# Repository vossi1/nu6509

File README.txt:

Nu6509 - Adapter to use 6502 in 6509-based systemOriginal Design: Copyright (c) 2017-2019 Jim Brain dba RETRO Innovations

Copyright (c) 2023 Vossi - v.1[fixed, modified, no '816 support!]www.mos6509.com

Permission is hereby granted, free of charge, to any person obtaining a copy
of this software and associated documentation files (the "Software"), to deal
in the Software without restriction, including without limitation the rights
to use, copy, modify, merge, publish, distribute, sublicense, and/or sell
copies of the Software, and to permit persons to whom the Software is
furnished to do so, subject to the following conditions:

The above copyright notice and this permission notice shall be included in all
copies or substantial portions of the Software.

THE SOFTWARE IS PROVIDED "AS IS", WITHOUT WARRANTY OF ANY KIND, EXPRESS OR
IMPLIED, INCLUDING BUT NOT LIMITED TO THE WARRANTIES OF MERCHANTABILITY,
FITNESS FOR A PARTICULAR PURPOSE AND NONINFRINGEMENT. IN NO EVENT SHALL THE
AUTHORS OR COPYRIGHT HOLDERS BE LIABLE FOR ANY CLAIM, DAMAGES OR OTHER
LIABILITY, WHETHER IN AN ACTION OF CONTRACT, TORT OR OTHERWISE, ARISING FROM,
OUT OF OR IN CONNECTION WITH THE SOFTWARE OR THE USE OR OTHER DEALINGS IN THE
SOFTWARE.

Nu6509.v: Routines to support mapping the 6509-specific bank functionality onto the 6502.    fixed:	databus read out always active if no WRITE (not only at PHI2=high, not dependent from RDY)	databus not dependent from RDY (ready is ignored at writes, wdc allows halt in write cycles)	databus writes not dependent from AEC (original 6509 doesn't disable DB with AEC)	hardwired sync (important for timing in P500)modified:	removed 65816 support	added jtag connector	only 0805 parts	hardwired _so	solderpad is pre-connected for NMOS/CMOS 6502 -> cut for WDC W65C02S

Tested successful in cbm620 with:
	mos6502A
	mos6502B (3MHz)
	R6502AP
	UM6502A
	UMC6502CE (4MHz, nmos)
	CMD G65SC02-2
	gte G65SC02-2
	WDC W65C02S-8 (8MHz)

Tests: Diagnostic-Cart, Burnin-Test, Michal's Testsuite, Superscript
	(all cmos chips have TOD error in cbm burnin test???)

Tested successful in P500 with:
	mos6502A
	mos6502B (3MHz)
	R6502
	R6502AP
	SY6502
	UM6502A
	UMC6502CE (4MHz)
	CMD G65SC02-2
	gte G65SC02-2
	WDC W65C02S-8 (8MHz)

Tests: PacMan, Wizard of War, cbm RAM-Test (improved by Vossi), David Viner's Hires-Demo

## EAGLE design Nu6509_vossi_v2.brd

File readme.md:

# Nu6509 - Adapter to use 6502 in 6509-based system

**Original Design: Copyright (c) 2017-2019 Jim Brain dba RETRO Innovations**

**Copyright (c) 2023 Vossi - v.2** [fixed, modified, 6512 support, no '816 support]

**www.mos6509.com**

Permission is hereby granted, free of charge, to any person obtaining a copy
of this software and associated documentation files (the "Software"), to deal
in the Software without restriction, including without limitation the rights
to use, copy, modify, merge, publish, distribute, sublicense, and/or sell
copies of the Software, and to permit persons to whom the Software is
furnished to do so, subject to the following conditions:

The above copyright notice and this permission notice shall be included in all
copies or substantial portions of the Software.

THE SOFTWARE IS PROVIDED "AS IS", WITHOUT WARRANTY OF ANY KIND, EXPRESS OR
IMPLIED, INCLUDING BUT NOT LIMITED TO THE WARRANTIES OF MERCHANTABILITY,
FITNESS FOR A PARTICULAR PURPOSE AND NONINFRINGEMENT. IN NO EVENT SHALL THE
AUTHORS OR COPYRIGHT HOLDERS BE LIABLE FOR ANY CLAIM, DAMAGES OR OTHER
LIABILITY, WHETHER IN AN ACTION OF CONTRACT, TORT OR OTHERWISE, ARISING FROM,
OUT OF OR IN CONNECTION WITH THE SOFTWARE OR THE USE OR OTHER DEALINGS IN THE
SOFTWARE.

**Nu6509.v: Routines to support mapping the 6509-specific bank functionality onto the 6502.**

**[Schematic](https://github.com/vossi1/nu6509/blob/master/schematics_v2.png)**

**[Parts](https://github.com/vossi1/nu6509/blob/master/parts.txt)**

**CPLD-Firmware:** The .JED file can be uploaded with a JTAG-SMT2 Xilinx programmer (China) and [xc3sprog](https://xc3sprog.sourceforge.net/)

**USE v.2 HDL-code in Folder HDL-P500 for the P500 - for the 6xx, 7xx v.2 and v.2a are ok**

**Fixed:**

	databus not dependent from RDY (ready is ignored at writes, wdc allows halt in write cycles)
	databus read and write with 30ns hold time after PHI2 falling edge
	hardwired SYNC (important for timing in P500)

**Modified:**

	removed 65816 support
	added jtag connector
	only 0805 parts
	hardwired _SO
	solderpad is pre-connected for NMOS/CMOS 6502 -> cut for WDC W65C02S
	added 6512 support with solderpad for PHI1 in from 6509 socket

:x: **BEWARE: XC9572 from China are mostly FAKES - many of them work - but you don't know what you get!**

Notes:
In low profile machines there is not enough space in the height to insert the adapter with socket. There is even less space in devices with a bottom-mounted power supply unit. The only solution is to first test the NU6509 in an open device and then solder it directly into the board.
The NU6509 does not support AEC! No known CBMII-machine uses it - AEC is always pulled up on all CBMII-boards.
If you encounter problems with a specific 6502 CPU, try another one - best choice is mostly an old mos 6502A.

**Tested successful in cbm2 with:** Diagnostic, Burnin-Test, Testsuite, Superscript, Monitor D.Viner, Supermon, Diskview

Test-boards: 610 Rev.E, 620 Rev.F, 710 Rev.B, 710 Rev.C, 720 Rev. B

	mos6502A
	mos6502AD
	mos6502B (3MHz)
	R6502AP
	UM6502A
	UM6502B (3MHz, nmos)
	UM6502CE (4MHz, nmos)
	R65C02P2 (cmos)
	R65C02-J4 (4MHz, cmos, in PLCC Adapter)
	gteµ G65SC02P-2 (cmos)
	CMD G65SC02PI-2 (cmos)
	CMD G65SC02PE-4 (4MHz, cmos, in PLCC Adapter)
	WDC W65C02S8PL-10 (10MHz, cmos, in PLCC Adapter)

	R6512AP (with Solderpad 6512 for PHI1 - needs the two-phase clock!)
	GTEµ G65SC12P-2 (2MHz, cmos) (with Solderpad 6512 for PHI1 - needs the two-phase clock!)

Note cmos: (all cmos chips have TOD error in the cbm2 burnin test - localized at indirect read from CIA registers - so they are probably unusable?)

**Tested successful in P500 EU with:** pm500, wiz500, amind500 (all converted by vossi), P500-Test (finished & improved by Vossi), David Viner's Hires-Demo

	mos6502
	mos6502AD
	mos6502A
	mos6502B (3MHz)
	R6502
	R6502AP
	SY6502
	UM6502
	UM6502A
	UM6502B (3MHz, nmos)
	UM6502CE (4MHz, nmos)
	R65C02P2 (cmos)
	R65C02-J4 (4MHz, cmos, in PLCC Adapter)
	gteµ G65SC02P-2 (cmos)
	CMD G65SC02PI-2 (cmos)
	CMD G65SC02PE-4 (4MHz, cmos, in PLCC Adapter)
	WDC W65C02S8PL-10 (10MHz, cmos, in PLCC Adapter)

	R6512AP (with Solderpad 6512 for PHI1 - needs the two-phase clock!)
	GTEµ G65SC12P-2 (with Solderpad 6512 for PHI1 - needs the two-phase clock!)

Note cmos: (amind 500 uses illegal opcodes and doesn't run on cmos CPU's)
Note cmos: (all cmos chips have also TOD error in my new P500-test v. 1.4 - so they are probably unusable?)

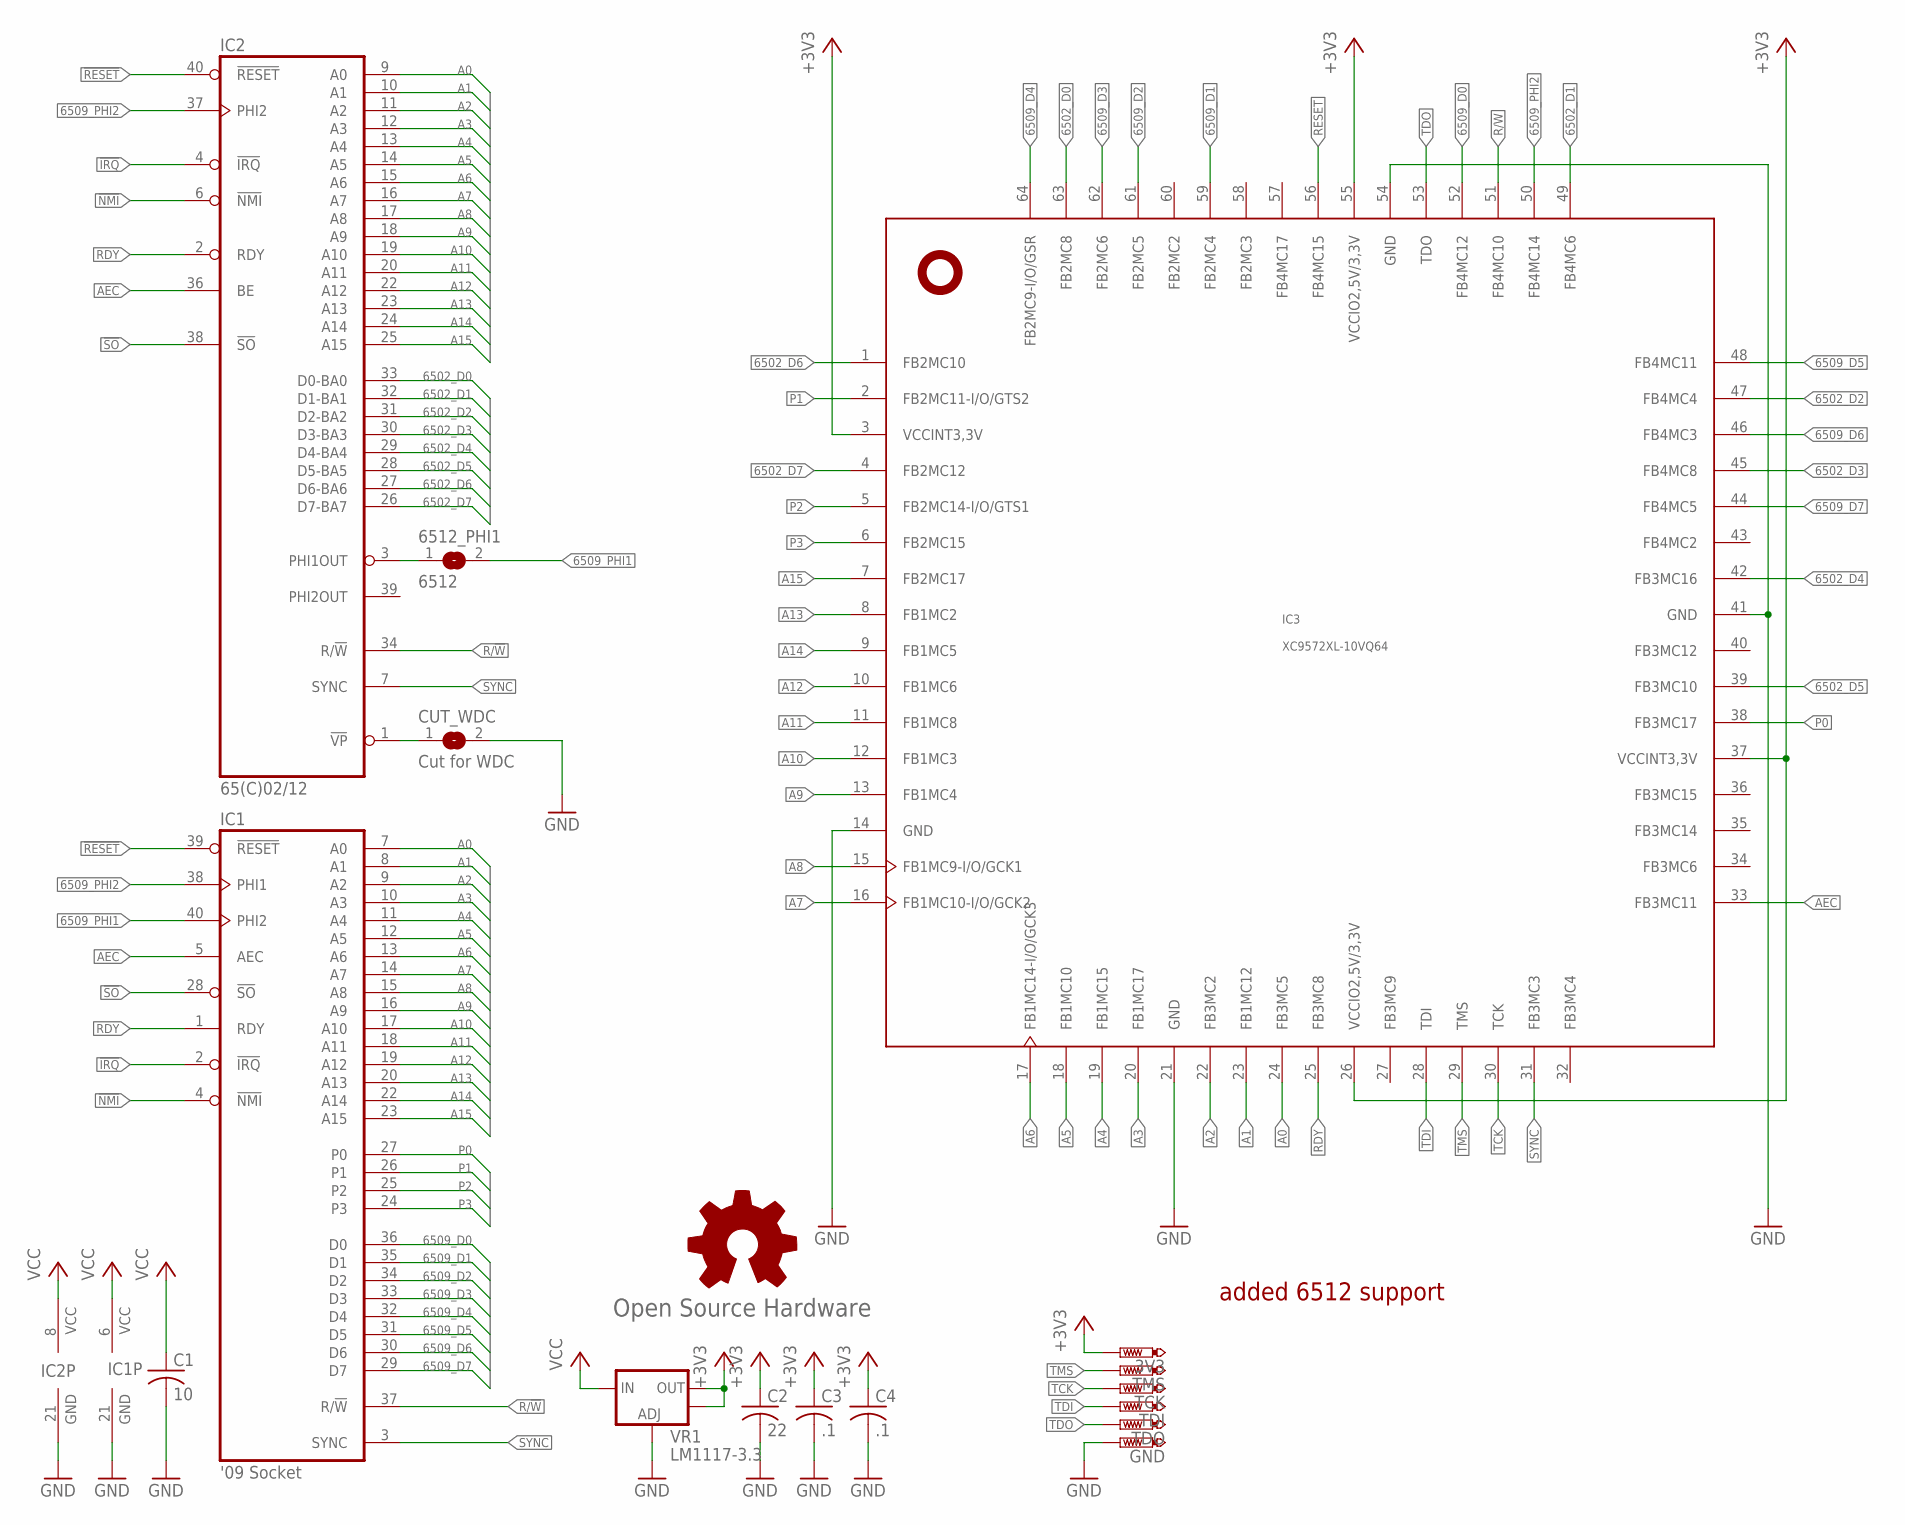
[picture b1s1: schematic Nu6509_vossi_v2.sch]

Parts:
3V3: PTR1TP08R; TP08R
6512_PHI1: 6512; SJ
C1: 10; C0805
C2: 22; C0805
C3, C4: .1; C0805
CUT_WDC: Cut for WDC; SJ
GND: PTR1TP08R; TP08R
GOLD_ORB_SM1: Open Source Hardware; OSHW_5MM
IC1: '09 Socket; DIL40-ROUNDPAD
IC2: 65(C)02/12; DIL40-ROUNDPAD
IC3: XC9572XL-10VQ64; VQFP64
TCK: PTR1TP08R; TP08R
TDI: PTR1TP08R; TP08R
TDO: PTR1TP08R; TP08R
TMS: PTR1TP08R; TP08R
VR1: LM1117-3.3; SOT223

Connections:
6502_D0: IC2.33 (D0-BA0), IC3.63 (FB2MC8)
6502_D1: IC2.32 (D1-BA1), IC3.49 (FB4MC6)
6502_D2: IC2.31 (D2-BA2), IC3.47 (FB4MC4)
6502_D3: IC2.30 (D3-BA3), IC3.45 (FB4MC8)
6502_D4: IC2.29 (D4-BA4), IC3.42 (FB3MC16)
6502_D5: IC2.28 (D5-BA5), IC3.39 (FB3MC10)
6502_D6: IC2.27 (D6-BA6), IC3.1 (FB2MC10)
6502_D7: IC2.26 (D7-BA7), IC3.4 (FB2MC12)
6502_VSS: CUT_WDC.1, IC2.1 (!VP)
6509_D0: IC1.36 (D0), IC3.52 (FB4MC12)
6509_D1: IC1.35 (D1), IC3.59 (FB2MC4)
6509_D2: IC1.34 (D2), IC3.61 (FB2MC5)
6509_D3: IC1.33 (D3), IC3.62 (FB2MC6)
6509_D4: IC1.32 (D4), IC3.64 (FB2MC9-I/O/GSR)
6509_D5: IC1.31 (D5), IC3.48 (FB4MC11)
6509_D6: IC1.30 (D6), IC3.46 (FB4MC3)
6509_D7: IC1.29 (D7), IC3.44 (FB4MC5)
6509_PHI1: 6512_PHI1.2, IC1.40 (PHI2)
6509_PHI2: IC1.38 (PHI1), IC2.37 (PHI2), IC3.50 (FB4MC14)
6512_PHI1: 6512_PHI1.1, IC2.3 (PHI1OUT)
!IRQ: IC1.2 (!IRQ), IC2.4 (!IRQ)
!NMI: IC1.4 (!NMI), IC2.6 (!NMI)
!RESET: IC1.39 (!RESET), IC2.40 (!RESET), IC3.56 (FB4MC15)
!SO: IC1.28 (!SO), IC2.38 (!SO)
+3V3: 3V3.TP, C2.1, C3.1, C4.1, IC3.3 (VCCINT3,3V), IC3.26 (VCCIO2,5V/3,3V), IC3.37 (VCCINT3,3V), IC3.55 (VCCIO2,5V/3,3V), VR1.2 (OUT), VR1.4 (OUT)
A0: IC1.7 (A0), IC2.9 (A0), IC3.24 (FB3MC5)
A1: IC1.8 (A1), IC2.10 (A1), IC3.23 (FB1MC12)
A2: IC1.9 (A2), IC2.11 (A2), IC3.22 (FB3MC2)
A3: IC1.10 (A3), IC2.12 (A3), IC3.20 (FB1MC17)
A4: IC1.11 (A4), IC2.13 (A4), IC3.19 (FB1MC15)
A5: IC1.12 (A5), IC2.14 (A5), IC3.18 (FB1MC10)
A6: IC1.13 (A6), IC2.15 (A6), IC3.17 (FB1MC14-I/O/GCK3)
A7: IC1.14 (A7), IC2.16 (A7), IC3.16 (FB1MC10-I/O/GCK2)
A8: IC1.15 (A8), IC2.17 (A8), IC3.15 (FB1MC9-I/O/GCK1)
A9: IC1.16 (A9), IC2.18 (A9), IC3.13 (FB1MC4)
A10: IC1.17 (A10), IC2.19 (A10), IC3.12 (FB1MC3)
A11: IC1.18 (A11), IC2.20 (A11), IC3.11 (FB1MC8)
A12: IC1.19 (A12), IC2.22 (A12), IC3.10 (FB1MC6)
A13: IC1.20 (A13), IC2.23 (A13), IC3.8 (FB1MC2)
A14: IC1.22 (A14), IC2.24 (A14), IC3.9 (FB1MC5)
A15: IC1.23 (A15), IC2.25 (A15), IC3.7 (FB2MC17)
AEC: IC1.5 (AEC), IC2.36 (BE), IC3.33 (FB3MC11)
GND: C1.2, C2.2, C3.2, C4.2, CUT_WDC.2, GND.TP, IC1.21 (GND), IC2.21 (GND), IC3.14 (GND), IC3.21 (GND), IC3.41 (GND), IC3.54 (GND), VR1.1 (ADJ)
P0: IC1.27 (P0), IC3.38 (FB3MC17)
P1: IC1.26 (P1), IC3.2 (FB2MC11-I/O/GTS2)
P2: IC1.25 (P2), IC3.5 (FB2MC14-I/O/GTS1)
P3: IC1.24 (P3), IC3.6 (FB2MC15)
R/!W: IC1.37 (R/!W), IC2.34 (R/!W), IC3.51 (FB4MC10)
RDY: IC1.1 (RDY), IC2.2 (RDY), IC3.25 (FB3MC8)
SYNC: IC1.3 (SYNC), IC2.7 (SYNC), IC3.31 (FB3MC3)
TCK: IC3.30 (TCK), TCK.TP
TDI: IC3.28 (TDI), TDI.TP
TDO: IC3.53 (TDO), TDO.TP
TMS: IC3.29 (TMS), TMS.TP
VCC: C1.1, IC1.6 (VCC), IC2.8 (VCC), VR1.3 (IN)

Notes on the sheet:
added 6512 support

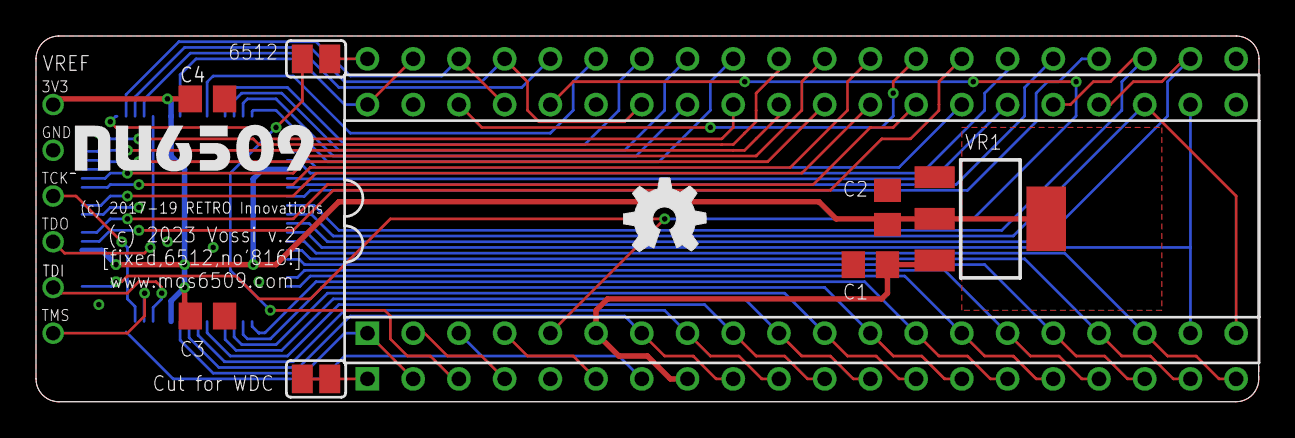
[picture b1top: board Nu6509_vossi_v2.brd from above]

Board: 2 copper layers, 67.9 x 20.3 mm, 17 parts (1 on the bottom side), 55 nets.

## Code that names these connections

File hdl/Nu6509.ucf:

#PACE: Start of Constraints generated by PACE

#PACE: Start of PACE I/O Pin Assignments
NET "_reset"  LOC = "P56"  ; 
NET "address_6502<0>"  LOC = "P24"  ; 
NET "address_6502<10>"  LOC = "P12"  ; 
NET "address_6502<11>"  LOC = "P11"  ; 
NET "address_6502<12>"  LOC = "P10"  ; 
NET "address_6502<13>"  LOC = "P8"  ; 
NET "address_6502<14>"  LOC = "P9"  ; 
NET "address_6502<15>"  LOC = "P7"  ; 
NET "address_6502<1>"  LOC = "P23"  ; 
NET "address_6502<2>"  LOC = "P22"  ; 
NET "address_6502<3>"  LOC = "P20"  ; 
NET "address_6502<4>"  LOC = "P19"  ; 
NET "address_6502<5>"  LOC = "P18"  ; 
NET "address_6502<6>"  LOC = "P17"  ; 
NET "address_6502<7>"  LOC = "P16"  ; 
NET "address_6502<8>"  LOC = "P15"  ; 
NET "address_6502<9>"  LOC = "P13"  ; 
NET "address_bank<0>"  LOC = "P38"  ; 
NET "address_bank<1>"  LOC = "P2"  ; 
NET "address_bank<2>"  LOC = "P5"  ; 
NET "address_bank<3>"  LOC = "P6"  ; 
#NET "aec"  LOC = "P33"  ; 
NET "data_6502<0>"  LOC = "P63"  ; 
NET "data_6502<1>"  LOC = "P49"  ; 
NET "data_6502<2>"  LOC = "P47"  ; 
NET "data_6502<3>"  LOC = "P45"  ; 
NET "data_6502<4>"  LOC = "P42"  ; 
NET "data_6502<5>"  LOC = "P39"  ; 
NET "data_6502<6>"  LOC = "P1"  ; 
NET "data_6502<7>"  LOC = "P4"  ; 
NET "data_6509<0>"  LOC = "P52"  ; 
NET "data_6509<1>"  LOC = "P59"  ; 
NET "data_6509<2>"  LOC = "P61"  ; 
NET "data_6509<3>"  LOC = "P62"  ; 
NET "data_6509<4>"  LOC = "P64"  ; 
NET "data_6509<5>"  LOC = "P48"  ; 
NET "data_6509<6>"  LOC = "P46"  ; 
NET "data_6509<7>"  LOC = "P44"  ; 
NET "phi2"  LOC = "P50"  ; 
NET "r_w"  LOC = "P51"  ; 
NET "rdy"  LOC = "P25"  ;
NET "sync"  LOC = "P31"  ; 

#PACE: Start of PACE Area Constraints

#PACE: Start of PACE Prohibit Constraints

#PACE: End of Constraints generated by PACE

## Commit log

2023-10-02 v1.0 initial version
2023-10-02 readme.md with photo
2023-10-02 readme.md format
2023-10-02 .git
2023-10-02 gerber
2023-10-08 added cpus
2023-10-16 added tested cpu's
2023-10-19 problems with cpu's
2023-10-24 tests with original xc9572xl
2023-10-25 added 6512 cmos
2023-10-28 layout v11 - unimportant design fixes
2023-10-28 layout v1
2023-11-16 v2 incl. 6512 support
2023-11-18 photo real v2
2024-02-07 notes
2024-02-11 comments hdl
2024-03-08 rewrote hdl
2024-03-09 partlist
2024-03-10 updated cpld order code
2024-11-24 added v.2 code again for p500
2025-01-10 added eagle files
2025-01-10 added firmware programming doc

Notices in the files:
Nu6509_vossi_v2.brd:
(c) 2017-19 RETRO Innovations
parts and their libraries:
SparkFun: Licensing: CC v3.0 Share-Alike You are welcome to use this library for commercial purposes.
